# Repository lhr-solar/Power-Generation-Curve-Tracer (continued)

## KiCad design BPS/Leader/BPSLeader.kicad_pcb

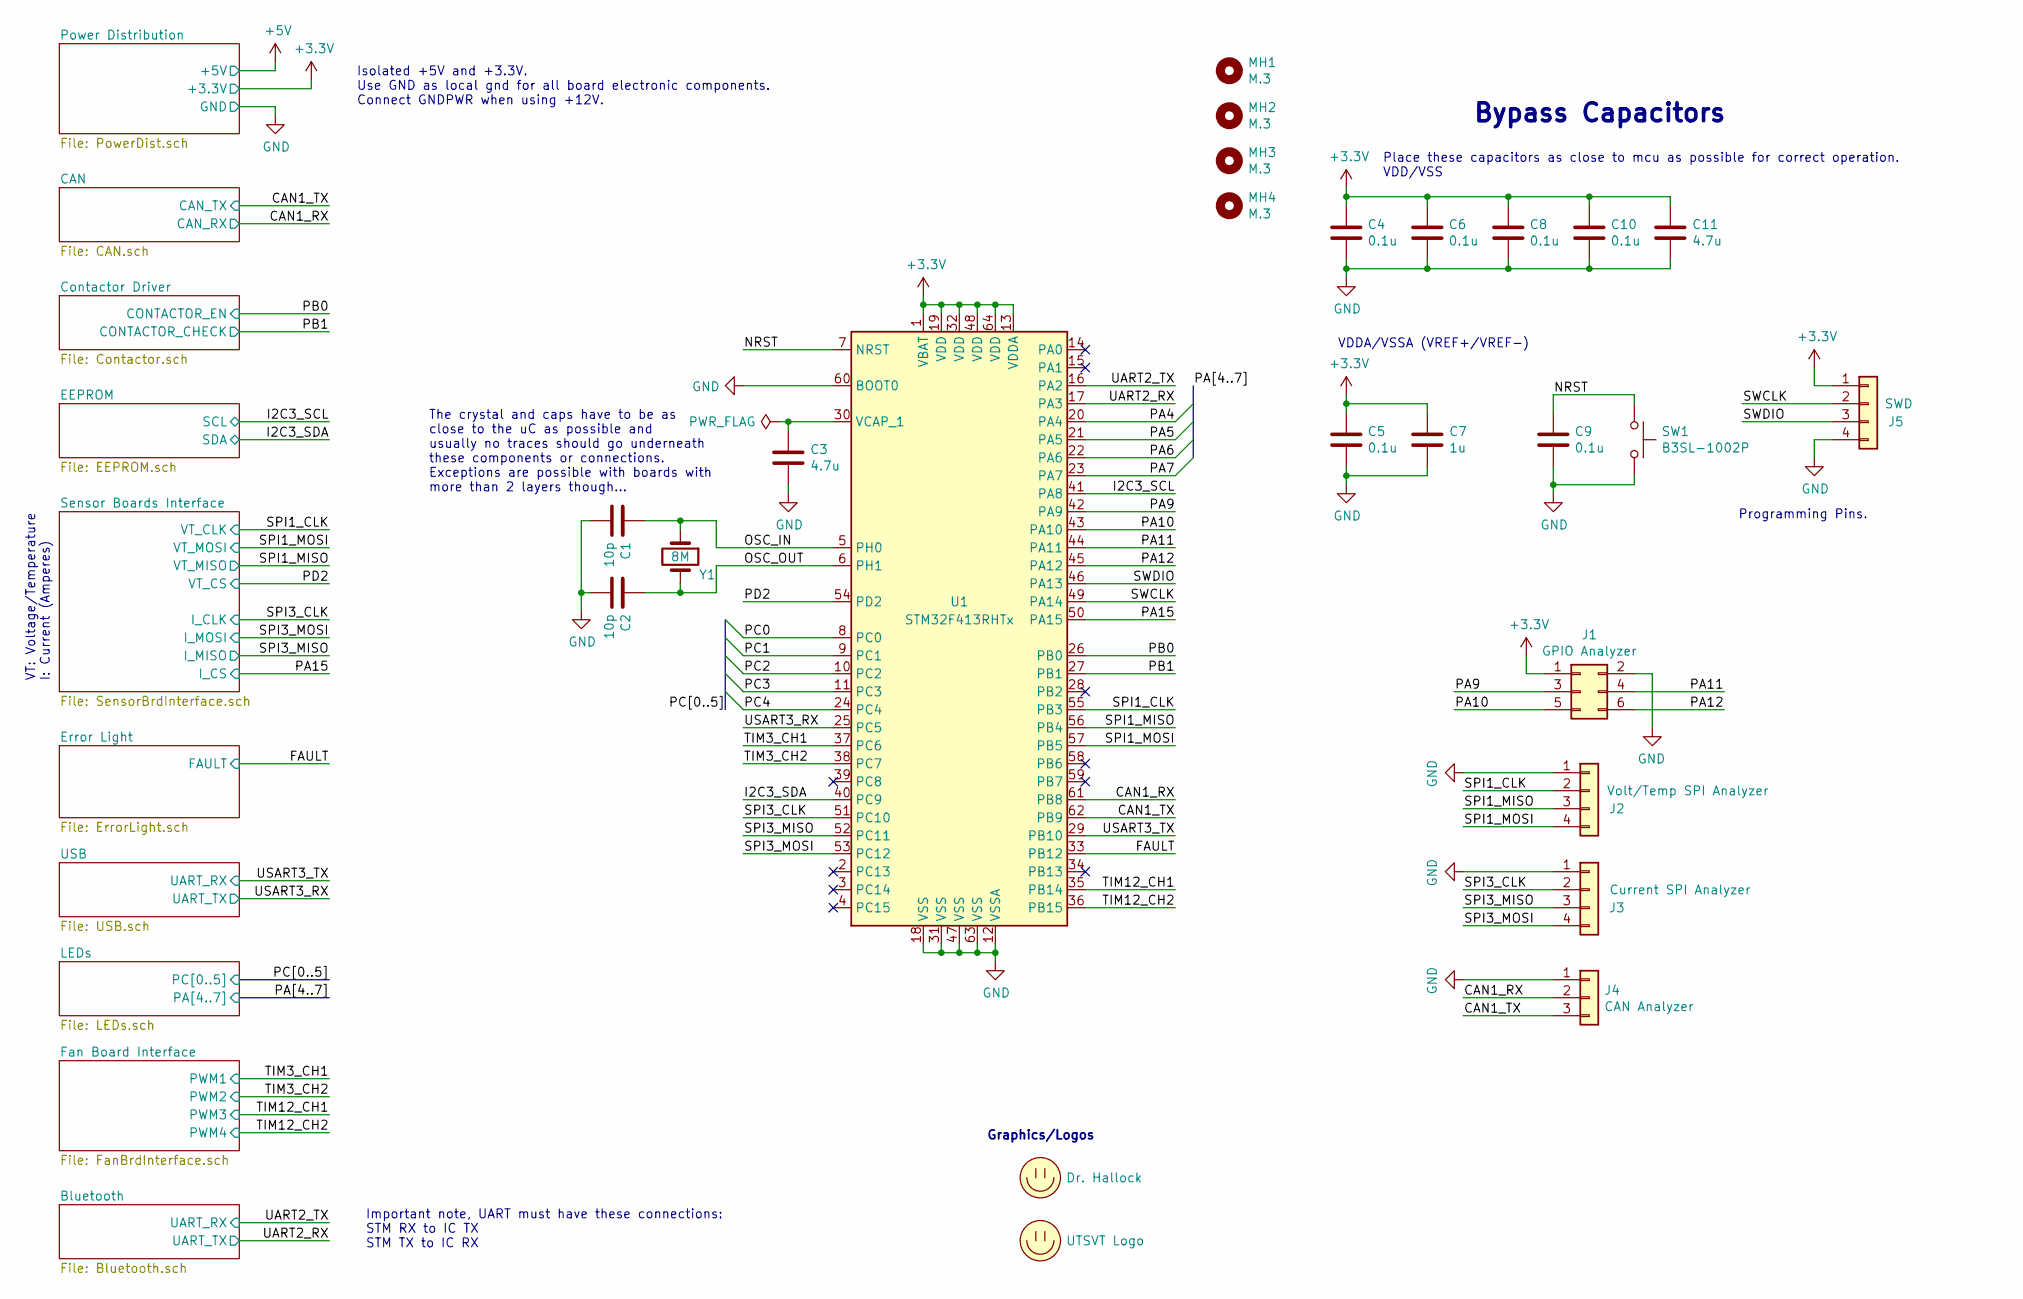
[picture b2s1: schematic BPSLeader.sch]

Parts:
C1, C2: 10p; C_0805_2012Metric
C3, C11: 4.7u; C_0805_2012Metric
C4, C5, C6, C8, C9, C10: 0.1u; C_0805_2012Metric
C7: 1u; C_0805_2012Metric
J1: GPIO Analyzer; PinHeader_2x03_P2.54mm_Vertical
J2: Volt/Temp SPI Analyzer; PinHeader_1x04_P2.54mm_Vertical
J3: Current SPI Analyzer; PinHeader_1x04_P2.54mm_Vertical
J4: CAN Analyzer; PinHeader_1x03_P2.54mm_Vertical
J5: SWD; PinHeader_1x04_P2.54mm_Vertical
LOGO1: Dr. Hallock; Hallock_Image_Small
LOGO2: UTSVT Logo; UTSVT_Logo_Symbol
MH1, MH2, MH3, MH4: M.3; MountingHole_3mm
SW1: B3SL-1002P; SW_SPST_B3SL-1002P
U1: STM32F413RHTx; LQFP-64_10x10mm_P0.5mm
Y1: 8M; Crystal_SMD_TXC_7A-2Pin_5x3.2mm

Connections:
+3V3: C4.1, C5.1, C6.1, C7.1, C8.1, C10.1, C11.1, J1.1, J5.1, U1.1 (VBAT), U1.13 (VDDA), U1.19 (VDD), U1.32 (VDD), U1.48 (VDD), U1.64 (VDD); also elsewhere on the board
/CAN1_RX: J4.2, U1.61 (PB8); also elsewhere on the board
/CAN1_TX: J4.3, U1.62 (PB9); also elsewhere on the board
/FAULT: U1.33 (PB12); also elsewhere on the board
/I2C3_SCL: U1.41 (PA8); also elsewhere on the board
/I2C3_SDA: U1.40 (PC9); also elsewhere on the board
/NRST: C9.1, SW1.1, U1.7 (NRST)
/OSC_IN: C1.1, U1.5 (PH0), Y1.1
/OSC_OUT: C2.1, U1.6 (PH1), Y1.2
/PA4: U1.20 (PA4); also elsewhere on the board
/PA5: U1.21 (PA5); also elsewhere on the board
/PA6: U1.22 (PA6); also elsewhere on the board
/PA7: U1.23 (PA7); also elsewhere on the board
/PA9: J1.3, U1.42 (PA9)
/PA10: J1.5, U1.43 (PA10)
/PA11: J1.4, U1.44 (PA11)
/PA12: J1.6, U1.45 (PA12)
/PA15: U1.50 (PA15); also elsewhere on the board
/PB0: U1.26 (PB0); also elsewhere on the board
/PB1: U1.27 (PB1); also elsewhere on the board
/PC0: U1.8 (PC0); also elsewhere on the board
/PC1: U1.9 (PC1); also elsewhere on the board
/PC2: U1.10 (PC2); also elsewhere on the board
/PC3: U1.11 (PC3); also elsewhere on the board
/PC4: U1.24 (PC4); also elsewhere on the board
/PD2: U1.54 (PD2); also elsewhere on the board
/SPI1_CLK: J2.2, U1.55 (PB3); also elsewhere on the board
/SPI1_MISO: J2.3, U1.56 (PB4); also elsewhere on the board
/SPI1_MOSI: J2.4, U1.57 (PB5); also elsewhere on the board
/SPI3_CLK: J3.2, U1.51 (PC10); also elsewhere on the board
/SPI3_MISO: J3.3, U1.52 (PC11); also elsewhere on the board
/SPI3_MOSI: J3.4, U1.53 (PC12); also elsewhere on the board
/SWCLK: J5.2, U1.49 (PA14)
/SWDIO: J5.3, U1.46 (PA13)
/TIM3_CH1: U1.37 (PC6); also elsewhere on the board
/TIM3_CH2: U1.38 (PC7); also elsewhere on the board
/TIM12_CH1: U1.35 (PB14); also elsewhere on the board
/TIM12_CH2: U1.36 (PB15); also elsewhere on the board
/UART2_RX: U1.17 (PA3); also elsewhere on the board
/UART2_TX: U1.16 (PA2); also elsewhere on the board
/USART3_RX: U1.25 (PC5); also elsewhere on the board
/USART3_TX: U1.29 (PB10); also elsewhere on the board
GND: C1.2, C2.2, C3.2, C4.2, C5.2, C6.2, C7.2, C8.2, C9.2, C10.2, C11.2, J1.2, J2.1, J3.1, J4.1, J5.4, SW1.2, U1.12 (VSSA), U1.18 (VSS), U1.31 (VSS), U1.47 (VSS), U1.60 (BOOT0), U1.63 (VSS); also elsewhere on the board
unnamed: C3.1, U1.30 (VCAP_1)

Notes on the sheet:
Place these capacitors as close to mcu as possible for correct operation. VDD/VSS
VDDA/VSSA (VREF+/VREF-)
Isolated +5V and +3.3V. Use GND as local gnd for all board electronic components. Connect GNDPWR when using +12V.
The crystal and caps have to be as close to the uC as possible and usually no traces should go underneath these components or connections. Exceptions are possible with boards with more than 2 layers though...
Programming Pins.
Bypass Capacitors
VT: Voltage/Temperature I: Current (Amperes)
Important note, UART must have these connections: STM RX to IC TX STM TX to IC RX
Graphics/Logos

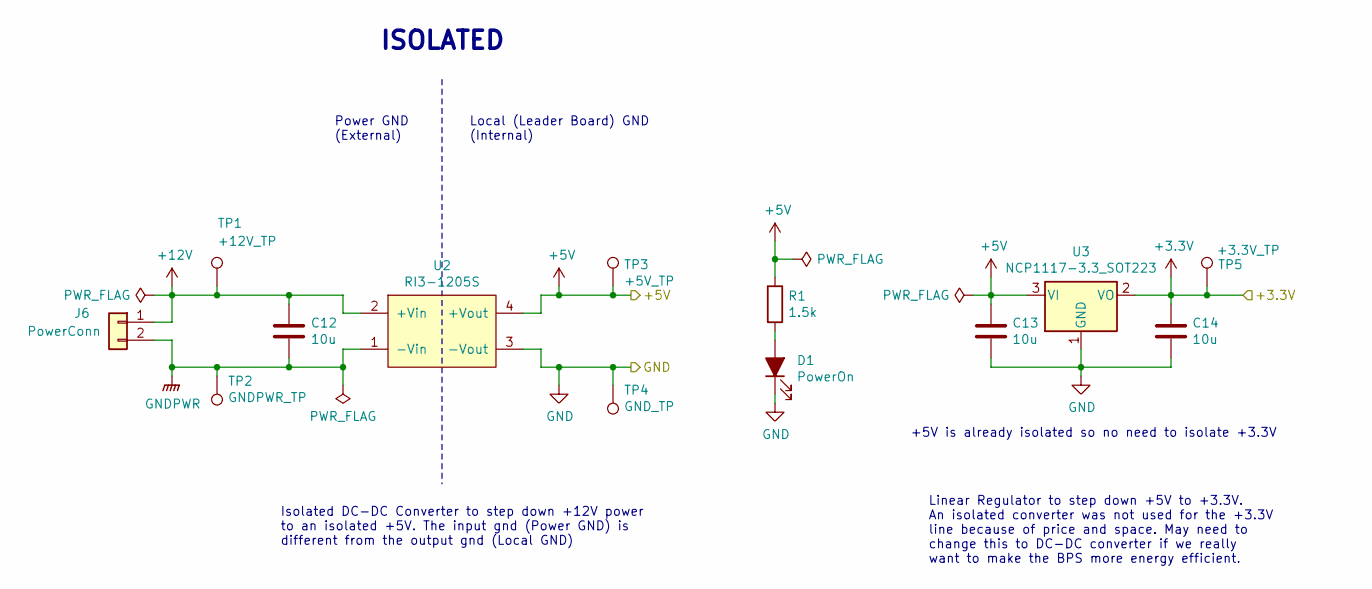
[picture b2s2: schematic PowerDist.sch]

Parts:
C12: 10u; C_2220_5750Metric
C13, C14: 10u; C_0805_2012Metric
D1: PowerOn; LED_0805_2012Metric
J6: PowerConn; Molex_MicroFit3.0_1x2xP3.00mm_PolarizingPeg_Vertical
R1: 1.5k; R_0805_2012Metric
TP1: +12V_TP; TestPoint_Keystone_5005-5009_Compact
TP2: GNDPWR_TP; TestPoint_Keystone_5005-5009_Compact
TP3: +5V_TP; TestPoint_Keystone_5005-5009_Compact
TP4: GND_TP; TestPoint_Keystone_5005-5009_Compact
TP5: +3.3V_TP; TestPoint_Keystone_5005-5009_Compact
U2: RI3-1205S; RI3_DC_Converter
U3: NCP1117-3.3_SOT223; SOT-223-3_TabPin2

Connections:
+3V3: C14.1, TP5.1, U3.2 (VO); also elsewhere on the board
+5V: C13.1, R1.1, TP3.1, U2.4 (+Vout), U3.3 (VI); also elsewhere on the board
+12V: C12.1, J6.1, TP1.1, U2.2 (+Vin); also elsewhere on the board
GND: C13.2, C14.2, D1.1 (K), TP4.1, U2.3 (-Vout), U3.1 (GND); also elsewhere on the board
GNDPWR: C12.2, J6.2, TP2.1, U2.1 (-Vin); also elsewhere on the board
unnamed: D1.2 (A), R1.2

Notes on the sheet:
+5V is already isolated so no need to isolate +3.3V
ISOLATED
Local (Leader Board) GND (Internal)
Power GND (External)
Linear Regulator to step down +5V to +3.3V. An isolated converter was not used for the +3.3V line because of price and space. May need to change this to DC-DC converter if we really want to make the BPS more energy efficient.
Isolated DC-DC Converter to step down +12V power to an isolated +5V. The input gnd (Power GND) is different from the output gnd (Local GND)

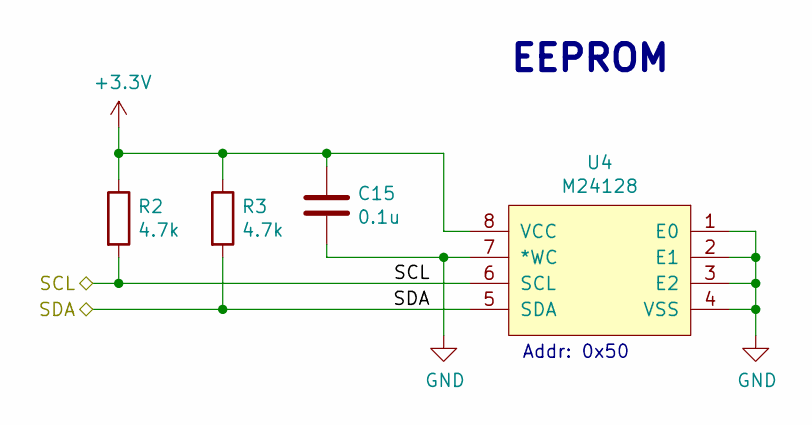
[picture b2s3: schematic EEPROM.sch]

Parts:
C15: 0.1u; C_0805_2012Metric
R2, R3: 4.7k; R_0805_2012Metric
U4: M24128; SOIC-8_3.9x4.9mm_P1.27mm

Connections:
+3V3: C15.1, R2.1, R3.1, U4.8 (VCC); also elsewhere on the board
/I2C3_SCL: R2.2, U4.6 (SCL); also elsewhere on the board
/I2C3_SDA: R3.2, U4.5 (SDA); also elsewhere on the board
GND: C15.2, U4.1 (E0), U4.2 (E1), U4.3 (E2), U4.4 (VSS), U4.7 (*WC); also elsewhere on the board

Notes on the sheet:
EEPROM
Addr: 0x50

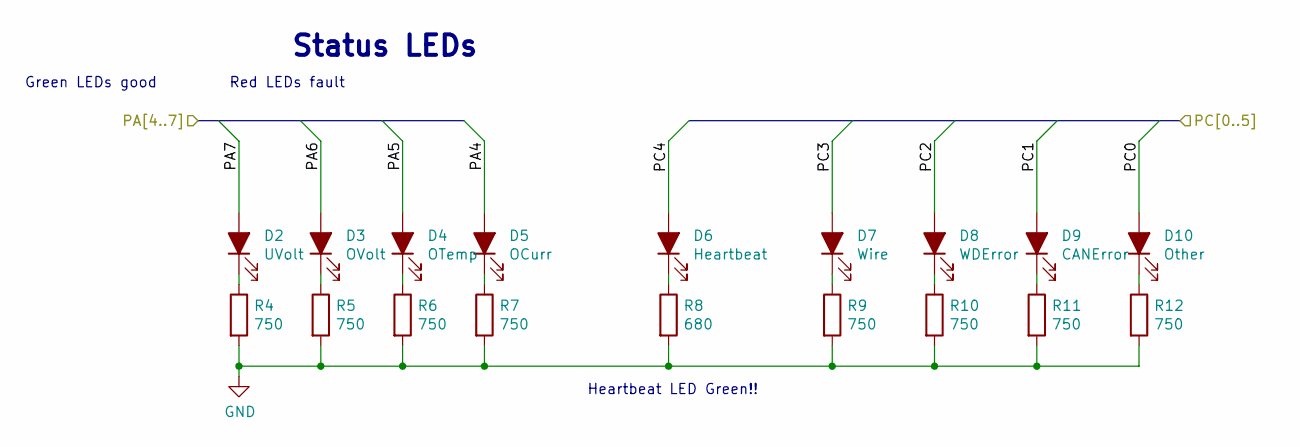
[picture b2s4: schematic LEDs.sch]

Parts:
D2: UVolt; LED_0805_2012Metric
D3: OVolt; LED_0805_2012Metric
D4: OTemp; LED_0805_2012Metric
D5: OCurr; LED_0805_2012Metric
D6: Heartbeat; LED_0805_2012Metric
D7: Wire; LED_0805_2012Metric
D8: WDError; LED_0805_2012Metric
D9: CANError; LED_0805_2012Metric
D10: Other; LED_0805_2012Metric
R4, R5, R6, R7, R9, R10, R11, R12: 750; R_0805_2012Metric
R8: 680; R_0805_2012Metric

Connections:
/PA4: D5.2 (A); also elsewhere on the board
/PA5: D4.2 (A); also elsewhere on the board
/PA6: D3.2 (A); also elsewhere on the board
/PA7: D2.2 (A); also elsewhere on the board
/PC0: D10.2 (A); also elsewhere on the board
/PC1: D9.2 (A); also elsewhere on the board
/PC2: D8.2 (A); also elsewhere on the board
/PC3: D7.2 (A); also elsewhere on the board
/PC4: D6.2 (A); also elsewhere on the board
GND: R4.2, R5.2, R6.2, R7.2, R8.2, R9.2, R10.2, R11.2, R12.2; also elsewhere on the board
unnamed: D2.1 (K), R4.1
unnamed: D3.1 (K), R5.1
unnamed: D4.1 (K), R6.1
unnamed: D5.1 (K), R7.1
unnamed: D6.1 (K), R8.1
unnamed: D7.1 (K), R9.1
unnamed: D8.1 (K), R10.1
unnamed: D9.1 (K), R11.1
unnamed: D10.1 (K), R12.1

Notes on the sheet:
Green LEDs good
Red LEDs fault
Status LEDs
Heartbeat LED Green!!

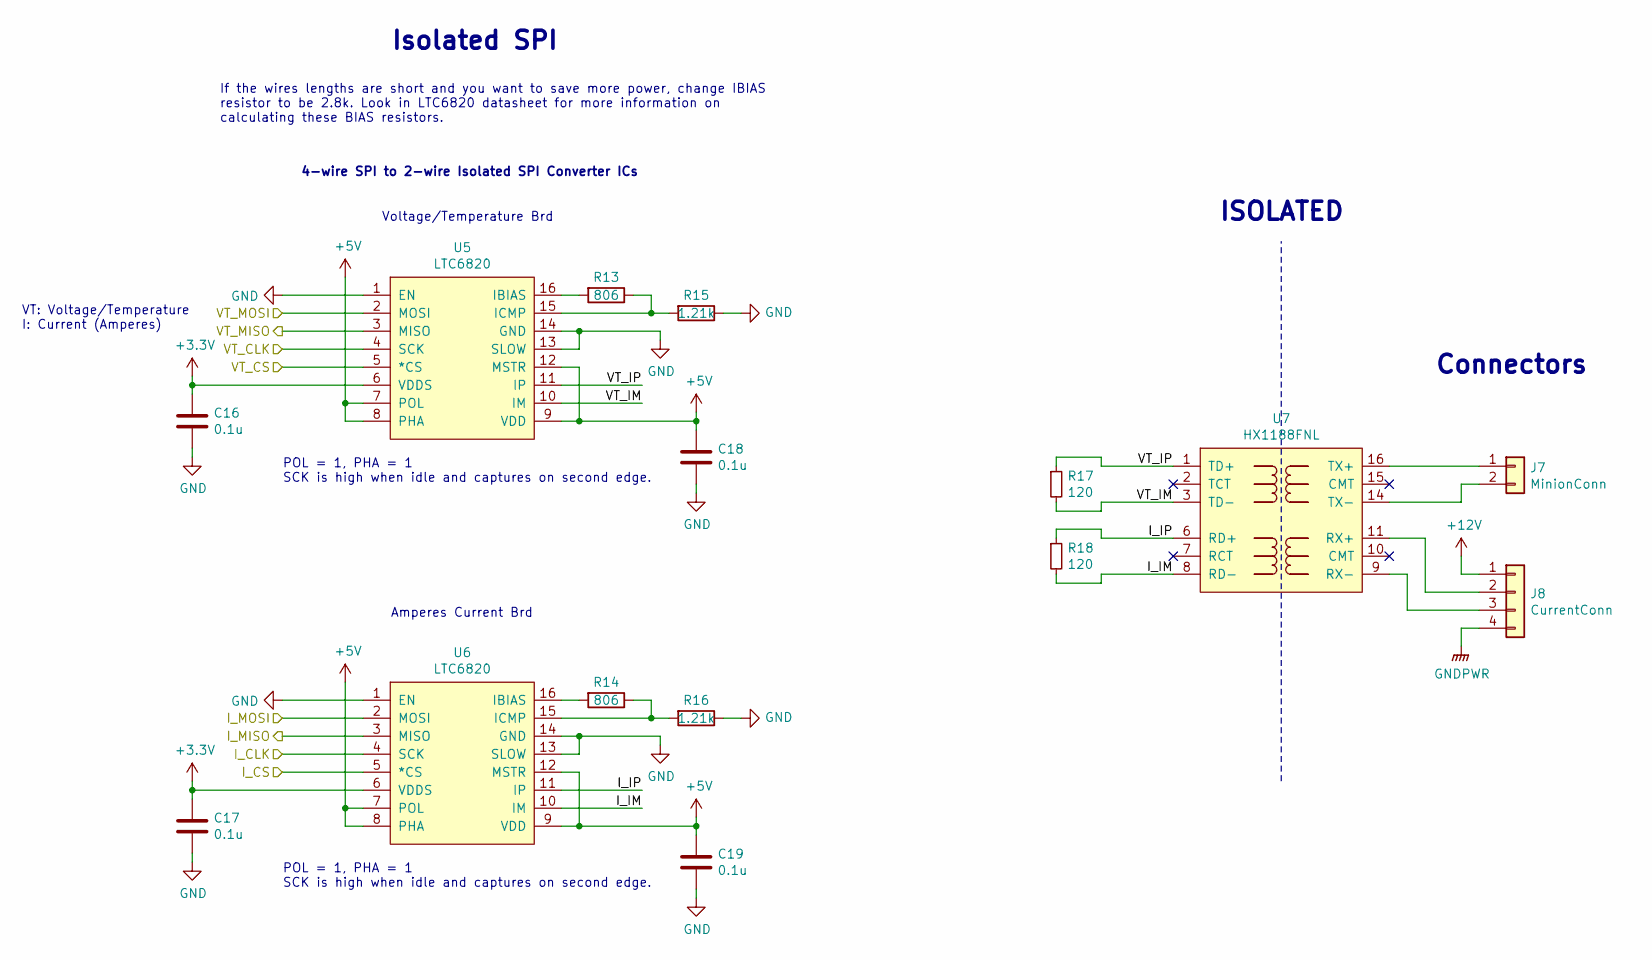
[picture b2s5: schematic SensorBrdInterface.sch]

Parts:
C16, C17, C18, C19: 0.1u; C_0805_2012Metric
J7: MinionConn; Molex_MicroFit3.0_1x2xP3.00mm_PolarizingPeg_Vertical
J8: CurrentConn; Molex_MicroFit3.0_1x4xP3.00mm_PolarizingPeg_Vertical
R13, R14: 806; R_0805_2012Metric
R15, R16: 1.21k; R_0805_2012Metric
R17, R18: 120; R_0805_2012Metric
U5, U6: LTC6820; MSOP-16_3x4mm_P0.5mm
U7: HX1188FNL; HXXXX

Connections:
+3V3: C16.1, C17.1, U5.6 (VDDS), U6.6 (VDDS); also elsewhere on the board
+5V: C18.1, C19.1, U5.7 (POL), U5.8 (PHA), U5.9 (VDD), U5.12 (MSTR), U6.7 (POL), U6.8 (PHA), U6.9 (VDD), U6.12 (MSTR); also elsewhere on the board
+12V: J8.1; also elsewhere on the board
/PA15: U6.5 (*CS); also elsewhere on the board
/PD2: U5.5 (*CS); also elsewhere on the board
/SPI1_CLK: U5.4 (SCK); also elsewhere on the board
/SPI1_MISO: U5.3 (MISO); also elsewhere on the board
/SPI1_MOSI: U5.2 (MOSI); also elsewhere on the board
/SPI3_CLK: U6.4 (SCK); also elsewhere on the board
/SPI3_MISO: U6.3 (MISO); also elsewhere on the board
/SPI3_MOSI: U6.2 (MOSI); also elsewhere on the board
/Sensor Boards Interface/I_IM: R18.2, U6.10 (IM), U7.8 (RD-)
/Sensor Boards Interface/I_IP: R18.1, U6.11 (IP), U7.6 (RD+)
/Sensor Boards Interface/VT_IM: R17.2, U5.10 (IM), U7.3 (TD-)
/Sensor Boards Interface/VT_IP: R17.1, U5.11 (IP), U7.1 (TD+)
GND: C16.2, C17.2, C18.2, C19.2, R15.1, R16.1, U5.1 (EN), U5.13 (SLOW), U5.14 (GND), U6.1 (EN), U6.13 (SLOW), U6.14 (GND); also elsewhere on the board
GNDPWR: J8.4; also elsewhere on the board
unnamed: J7.1, U7.16 (TX+)
unnamed: J7.2, U7.14 (TX-)
unnamed: J8.2, U7.11 (RX+)
unnamed: J8.3, U7.9 (RX-)
unnamed: R13.1, R15.2, U5.15 (ICMP)
unnamed: R13.2, U5.16 (IBIAS)
unnamed: R14.1, R16.2, U6.15 (ICMP)
unnamed: R14.2, U6.16 (IBIAS)

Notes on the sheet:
POL = 1, PHA = 1 SCK is high when idle and captures on second edge.
If the wires lengths are short and you want to save more power, change IBIAS resistor to be 2.8k. Look in LTC6820 datasheet for more information on calculating these BIAS resistors.
Isolated SPI
Amperes Current Brd
Voltage/Temperature Brd
VT: Voltage/Temperature I: Current (Amperes)
Connectors
ISOLATED
4-wire SPI to 2-wire Isolated SPI Converter ICs

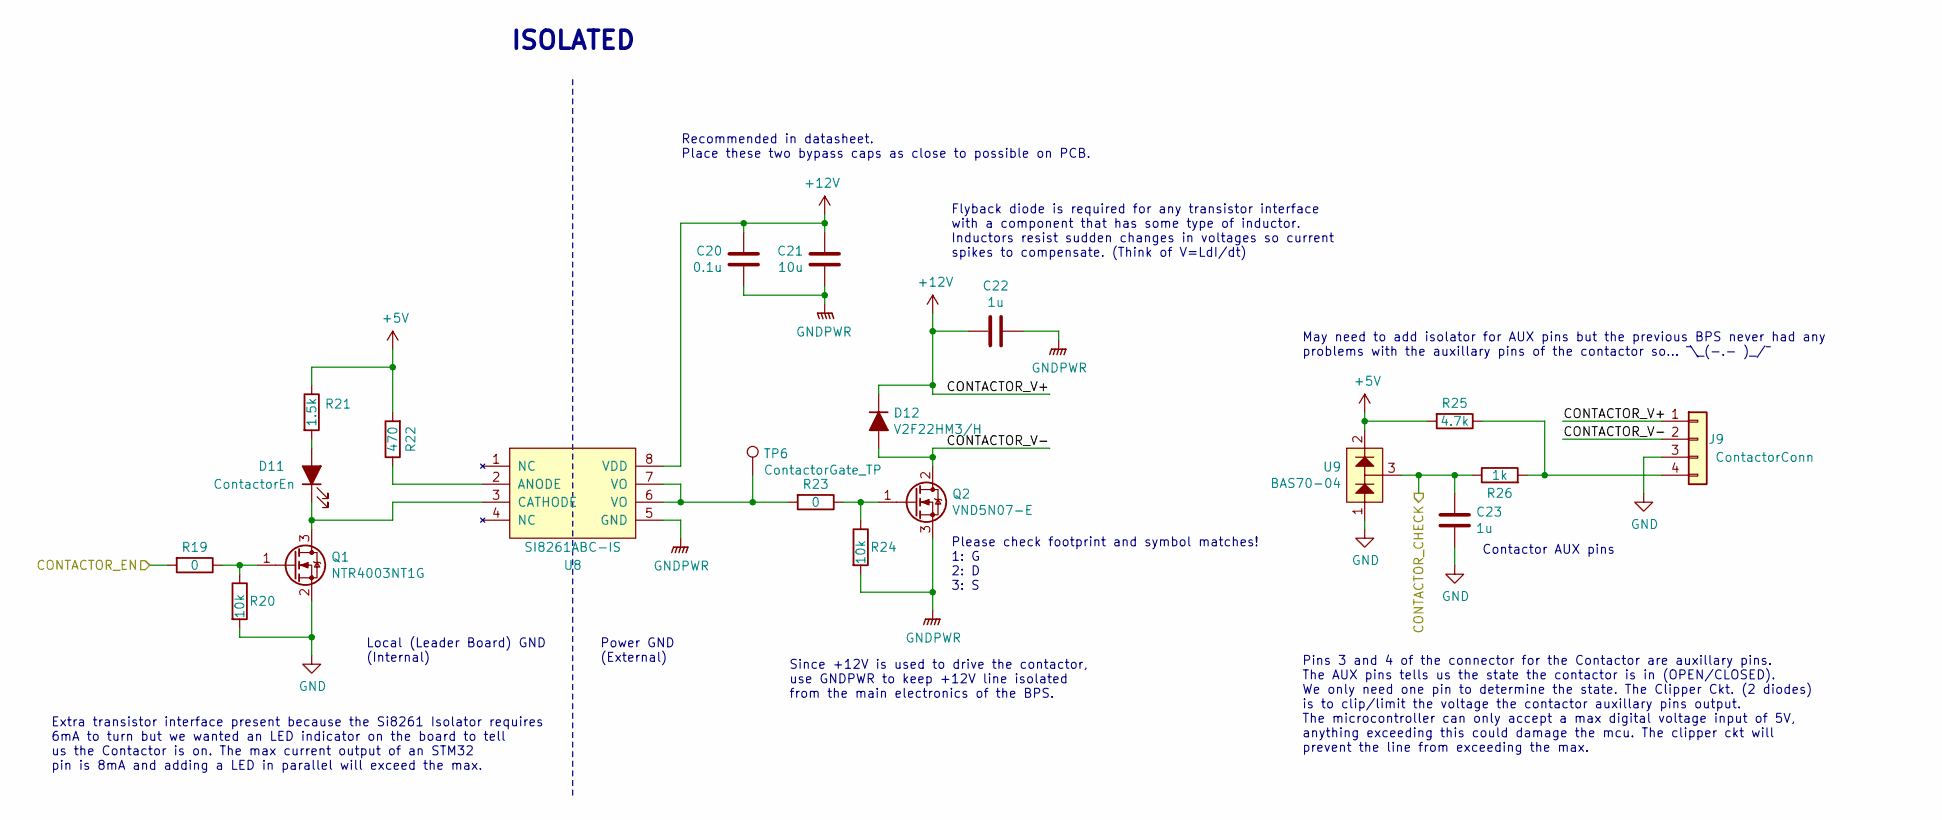
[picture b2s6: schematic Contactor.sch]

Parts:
C20: 0.1u; C_0805_2012Metric
C21: 10u; C_0805_2012Metric
C22, C23: 1u; C_0805_2012Metric
D11: ContactorEn; LED_0805_2012Metric
D12: V2F22HM3/H; V2F22HM
J9: ContactorConn; Molex_MicroFit3.0_1x4xP3.00mm_PolarizingPeg_Vertical
Q1: NTR4003NT1G; SOT-23
Q2: VND5N07-E; TO-252-2
R19, R23: 0; R_0805_2012Metric
R20, R24: 10k; R_0805_2012Metric
R21: 1.5k; R_0805_2012Metric
R22: 470; R_0805_2012Metric
R25: 4.7k; R_0805_2012Metric
R26: 1k; R_0805_2012Metric
TP6: ContactorGate_TP; TestPoint_Keystone_5005-5009_Compact
U8: SI8261ABC-IS; SOIC-8_3.9x4.9mm_P1.27mm
U9: BAS70-04; SOT-23

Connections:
+5V: R21.1, R22.2, R25.2, U9.2; also elsewhere on the board
+12V: C20.1, C21.1, C22.2, D12.1 (K), J9.1, U8.8 (VDD); also elsewhere on the board
/Contactor Driver/CONTACTOR_V-: D12.2 (A), J9.2, Q2.2 (D)
/PB0: R19.2; also elsewhere on the board
/PB1: C23.1, R26.1, U9.3; also elsewhere on the board
GND: C23.2, J9.3, Q1.2 (S), R20.2, U9.1; also elsewhere on the board
GNDPWR: C20.2, C21.2, C22.1, Q2.3 (S), R24.2, U8.5 (GND); also elsewhere on the board
unnamed: D11.1 (K), Q1.3 (D), U8.3 (CATHODE)
unnamed: D11.2 (A), R21.2
unnamed: J9.4, R25.1, R26.2
unnamed: Q1.1 (G), R19.1, R20.1
unnamed: Q2.1 (G), R23.1, R24.1
unnamed: R22.1, U8.2 (ANODE)
unnamed: R23.2, TP6.1, U8.6 (VO), U8.7 (VO)

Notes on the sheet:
Since +12V is used to drive the contactor, use GNDPWR to keep +12V line isolated from the main electronics of the BPS.
Recommended in datasheet. Place these two bypass caps as close to possible on PCB.
Please check footprint and symbol matches! 1: G 2: D 3: S
Extra transistor interface present because the Si8261 Isolator requires 6mA to turn but we wanted an LED indicator on the board to tell us the Contactor is on. The max current output of an STM32 pin is 8mA and adding a LED in parallel will exceed the max.
Pins 3 and 4 of the connector for the Contactor are auxillary pins. The AUX pins tells us the state the contactor is in (OPEN/CLOSED). We only need one pin to determine the state. The Clipper Ckt. (2 diodes) is to clip/limit the voltage the contactor auxillary pins output. The microcontroller can o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
Contactor AUX pins
Flyback diode is required for any transistor interface with a component that has some type of inductor. Inductors resist sudden changes in voltages so current spikes to compensate. (Think of V=LdI/dt)
May need to add isolator for AUX pins but the previous BPS never had any problems with the auxillary pins of the contactor so... ¯\_(-.- )_/¯
ISOLATED
Power GND (External)
Local (Leader Board) GND (Internal)

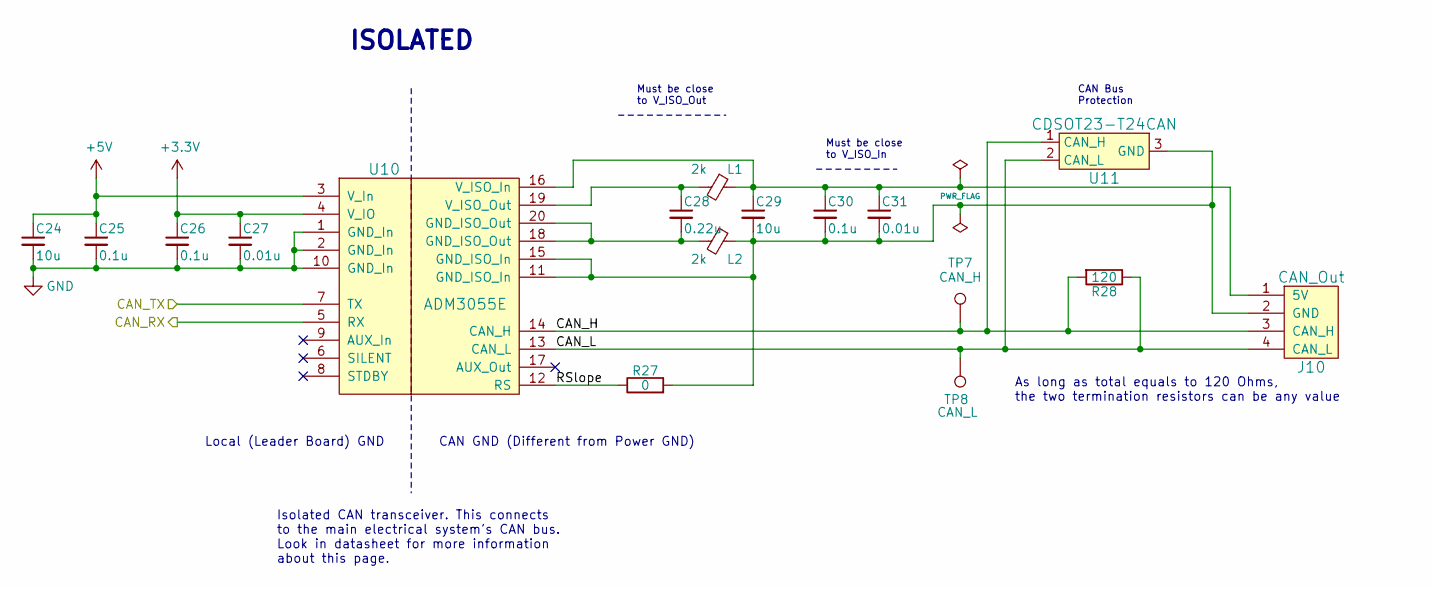
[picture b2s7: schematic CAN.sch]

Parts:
C24, C29: 10u; C_0805_2012Metric
C25, C26, C30: 0.1u; C_0805_2012Metric
C27, C31: 0.01u; C_0805_2012Metric
C28: 0.22u; C_0805_2012Metric
J10: CAN_Out; Molex_MicroFit3.0_1x4xP3.00mm_PolarizingPeg_Vertical
L1, L2: 2k; L_0805_2012Metric
R27: 0; R_0805_2012Metric
R28: 120; R_0805_2012Metric
TP7: CAN_H; TestPoint_Keystone_5005-5009_Compact
TP8: CAN_L; TestPoint_Keystone_5005-5009_Compact
U10: ADM3055E; SOIC-20W_7.5x15.4mm_Pitch1.27mm
U11: CDSOT23-T24CAN; SOT-23W

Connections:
+3V3: C26.1, C27.1, U10.4 (V_IO); also elsewhere on the board
+5V: C24.1, C25.1, U10.3 (V_In); also elsewhere on the board
/CAN1_RX: U10.5 (RX); also elsewhere on the board
/CAN1_TX: U10.7 (TX); also elsewhere on the board
/CAN/CAN_H: J10.3 (CAN_H), R28.2, TP7.1, U10.14 (CAN_H), U11.1 (CAN_H)
/CAN/CAN_L: J10.4 (CAN_L), R28.1, TP8.1, U10.13 (CAN_L), U11.2 (CAN_L)
/CAN/RSlope: R27.1, U10.12 (RS)
GND: C24.2, C25.2, C26.2, C27.2, U10.1 (GND_In), U10.2 (GND_In), U10.10 (GND_In); also elsewhere on the board
unnamed: C28.1, L1.2, U10.19 (V_ISO_Out)
unnamed: C28.2, L2.2, U10.18 (GND_ISO_Out), U10.20 (GND_ISO_Out)
unnamed: C29.1, C30.1, C31.1, J10.1 (5V), L1.1, U10.16 (V_ISO_In)
unnamed: C29.2, C30.2, C31.2, J10.2 (GND), L2.1, R27.2, U10.11 (GND_ISO_In), U10.15 (GND_ISO_In), U11.3 (GND)

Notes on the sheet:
Must be close to V_ISO_Out
Must be close to V_ISO_In
CAN Bus Protection
As long as total equals to 120 Ohms, the two termination resistors can be any value
ISOLATED
Local (Leader Board) GND
CAN GND (Different from Power GND)
Isolated CAN transceiver. This connects to the main electrical system's CAN bus. Look in datasheet for more information about this page.

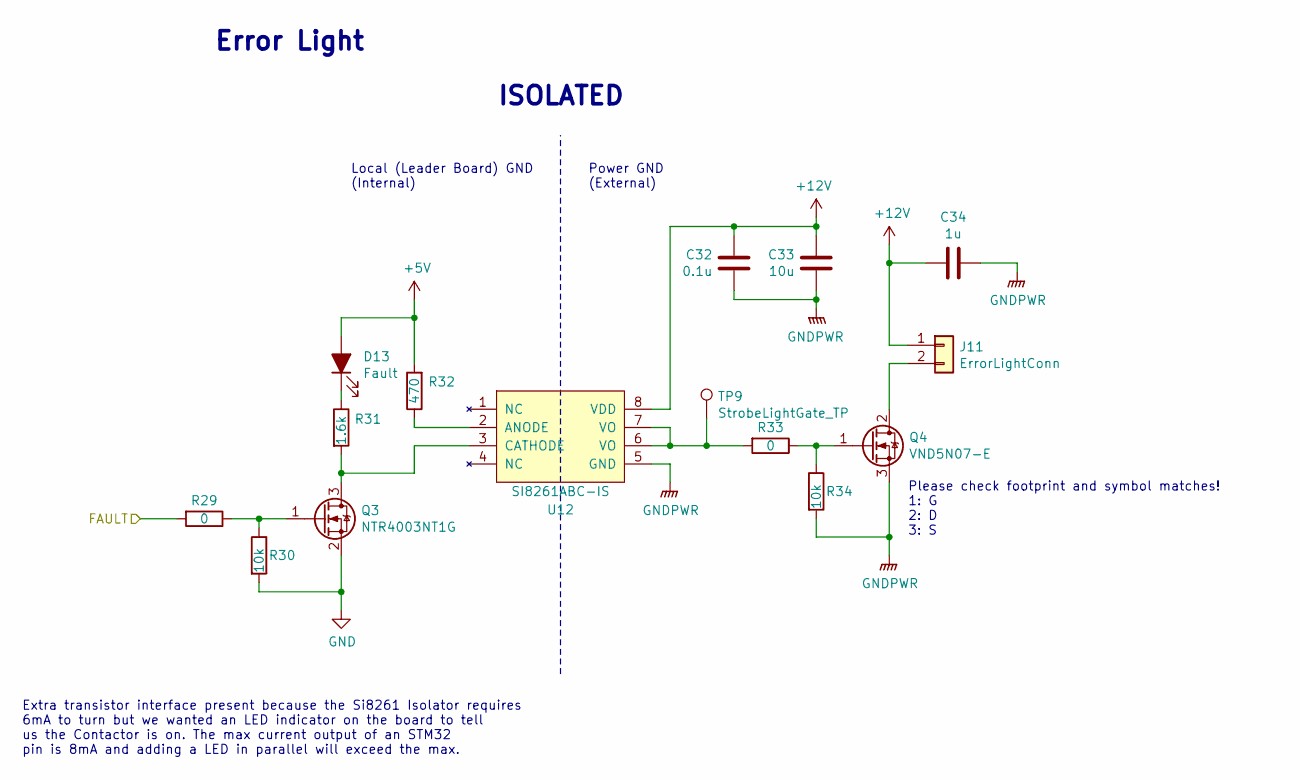
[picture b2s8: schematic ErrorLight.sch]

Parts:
C32: 0.1u; C_0805_2012Metric
C33: 10u; C_0805_2012Metric
C34: 1u; C_0805_2012Metric
D13: Fault; LED_0805_2012Metric
J11: ErrorLightConn; Molex_MicroFit3.0_1x2xP3.00mm_PolarizingPeg_Vertical
Q3: NTR4003NT1G; SOT-23
Q4: VND5N07-E; TO-252-2
R29, R33: 0; R_0805_2012Metric
R30, R34: 10k; R_0805_2012Metric
R31: 1.6k; R_0805_2012Metric
R32: 470; R_0805_2012Metric
TP9: StrobeLightGate_TP; TestPoint_Keystone_5005-5009_Compact
U12: SI8261ABC-IS; SOIC-8_3.9x4.9mm_P1.27mm

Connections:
+5V: D13.2 (A), R32.2; also elsewhere on the board
+12V: C32.1, C33.1, C34.2, J11.1, U12.8 (VDD); also elsewhere on the board
/FAULT: R29.2; also elsewhere on the board
GND: Q3.2 (S), R30.2; also elsewhere on the board
GNDPWR: C32.2, C33.2, C34.1, Q4.3 (S), R34.2, U12.5 (GND); also elsewhere on the board
unnamed: D13.1 (K), R31.1
unnamed: J11.2, Q4.2 (D)
unnamed: Q3.1 (G), R29.1, R30.1
unnamed: Q3.3 (D), R31.2, U12.3 (CATHODE)
unnamed: Q4.1 (G), R33.1, R34.1
unnamed: R32.1, U12.2 (ANODE)
unnamed: R33.2, TP9.1, U12.6 (VO), U12.7 (VO)

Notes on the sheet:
Error Light
Please check footprint and symbol matches! 1: G 2: D 3: S
Extra transistor interface present because the Si8261 Isolator requires 6mA to turn but we wanted an LED indicator on the board to tell us the Contactor is on. The max current output of an STM32 pin is 8mA and adding a LED in parallel will exceed the max.
ISOLATED
Local (Leader Board) GND (Internal)
Power GND (External)

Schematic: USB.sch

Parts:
C35: 4.7u; C_0805_2012Metric
C36: 0.1u; C_0805_2012Metric
D14: SP0503BAHT; SOT-143
J12: USB_B_Micro; USB_Micro-B_Molex-105017-0001
R35: 22.1k; R_0805_2012Metric
R36: 47.5k; R_0805_2012Metric
R37: 1k; R_0805_2012Metric
U13: CP2102N-A01-GQFN24; QFN-24-1EP_4x4mm_P0.5mm_EP2.6x2.6mm

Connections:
+3V3: C35.1, C36.1, R37.1, U13.5 (VIO), U13.6 (VDD), U13.7 (REGIN); also elsewhere on the board
/USART3_RX: U13.21 (TXD); also elsewhere on the board
/USART3_TX: U13.20 (RXD); also elsewhere on the board
GND: C35.2, C36.2, D14.1 (A), J12.5 (GND), J12.6 (Shield), R36.2, U13.2 (GND), U13.25 (GND); also elsewhere on the board
unnamed: D14.2 (K), J12.1 (VBUS), R35.2
unnamed: D14.3 (K), J12.2 (D-), U13.4 (D-)
unnamed: D14.4 (K), J12.3 (D+), U13.3 (D+)
unnamed: R35.1, R36.1, U13.8 (VBUS)
unnamed: R37.2, U13.9 (~RSTb)

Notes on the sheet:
The microcontroller should have Rx connected to UART_TX and Tx connected to UART_RX

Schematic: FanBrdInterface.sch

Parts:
C37, C38, C39, C40: 0.1u; C_0805_2012Metric
C41: 10u; C_0805_2012Metric
J13: FanBrdConn; Molex_Micro-Fit_3.0_43045-0612_2x03_P3.00mm_Vertical
R38, R39, R40, R41: 117; R_0805_2012Metric
U14, U15, U16, U17: SI8261ABC-IS; SOIC-8_3.9x4.9mm_P1.27mm

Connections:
+12V: C37.1, C38.1, C39.1, C40.1, C41.1, J13.1, U14.8 (VDD), U15.8 (VDD), U16.8 (VDD), U17.8 (VDD); also elsewhere on the board
/Fan Board Interface/FAN1: J13.2, U14.6 (VO), U14.7 (VO)
/Fan Board Interface/FAN2: J13.3, U15.6 (VO), U15.7 (VO)
/Fan Board Interface/FAN3: J13.5, U16.6 (VO), U16.7 (VO)
/Fan Board Interface/FAN4: J13.6, U17.6 (VO), U17.7 (VO)
/TIM3_CH1: R38.2; also elsewhere on the board
/TIM3_CH2: R39.2; also elsewhere on the board
/TIM12_CH1: R40.2; also elsewhere on the board
/TIM12_CH2: R41.2; also elsewhere on the board
GND: U14.3 (CATHODE), U15.3 (CATHODE), U16.3 (CATHODE), U17.3 (CATHODE); also elsewhere on the board
GNDPWR: C37.2, C38.2, C39.2, C40.2, C41.2, J13.4, U14.5 (GND), U15.5 (GND), U16.5 (GND), U17.5 (GND); also elsewhere on the board
unnamed: R38.1, U14.2 (ANODE)
unnamed: R39.1, U15.2 (ANODE)
unnamed: R40.1, U16.2 (ANODE)
unnamed: R41.1, U17.2 (ANODE)

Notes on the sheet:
Recommended in datasheet. Place these two bypass caps as close to possible on PCB.
All pins on this connector are isolated from the rest of the local components on this leader board.
ISOLATED
Local (Leader Board) GND
Power GND

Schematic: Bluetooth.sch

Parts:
C42: 1u; C_0805_2012Metric
C43: 0.1u; C_0805_2012Metric
R42: 4.7k; R_0805_2012Metric
U18: MCP112; SOT-23
U19: RN4871-I; Microchip_RN4871

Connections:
+3V3: C43.2, R42.1, U18.3 (VDD), U19.14 (VBAT); also elsewhere on the board
/UART2_RX: U19.8 (UART_TX); also elsewhere on the board
/UART2_TX: U19.7 (UART_RX); also elsewhere on the board
GND: C42.2, C43.1, U18.2 (VSS), U19.2 (GND), U19.13 (GND); also elsewhere on the board
unnamed: C42.1, R42.2, U18.1 (VOUT), U19.10 (RST)

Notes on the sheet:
Internal antenna used.
Reset Circuitry. This component prevents brownouts. As a note, the STM32 already has brownout prevention circuitry present internally so no need for this on the STM32.

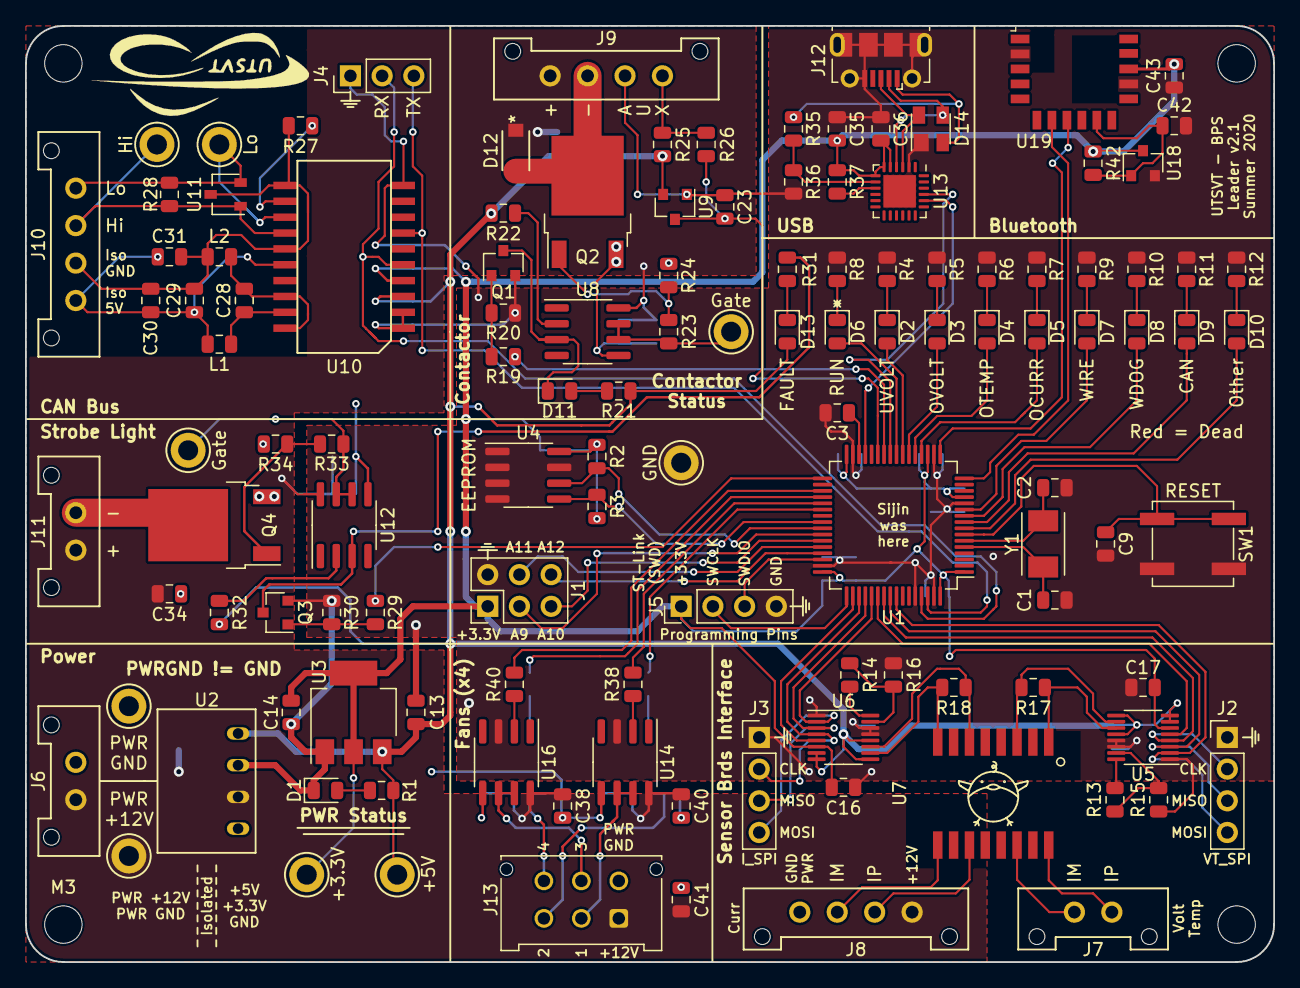
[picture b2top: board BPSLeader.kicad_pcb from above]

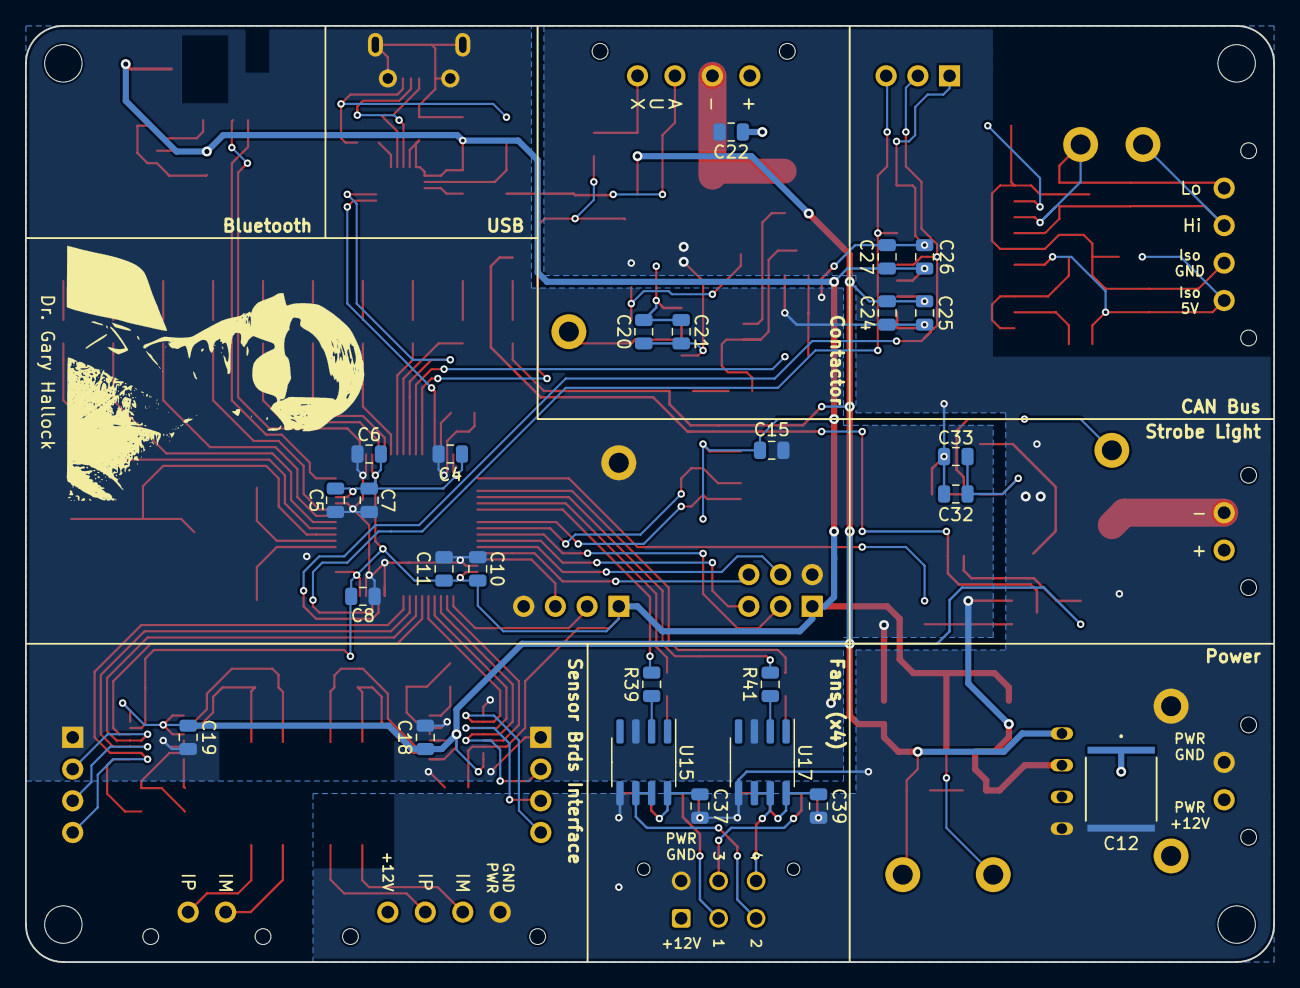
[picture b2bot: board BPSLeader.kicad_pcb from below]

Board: 2 copper layers, 100.0 x 75.0 mm, 154 parts (27 on the bottom side), 105 nets.
